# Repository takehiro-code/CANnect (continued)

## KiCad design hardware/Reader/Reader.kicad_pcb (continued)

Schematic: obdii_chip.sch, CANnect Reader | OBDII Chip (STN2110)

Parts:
CP_STN_1: 10uF; CP_Elec_4x5.8; Part Name EEEFP1E100AR; digikeypn PCE4539CT-ND
C_STN_1, C_STN_4, C_STN_5, C_STN_6: 1uF; 0603; Part Name C0603C105K4RACTU; digikeypn 399-7847-1-ND
C_STN_2, C_STN_3: 30pF; CAPC1608X90N; Part Name C0603C300J5GACTU; digikeypn 399-9057-1-ND
J_STN_1, J_STN_2, J_STN_4, J_STN_5, J_STN_6: Header_Pin_2; PinHeader_1x02_P2.54mm_Vertical
LED_STN_1: Status; LED_0603_1608Metric; Part Name 150060RS75000; digikeypn 732-4978-1-ND
LED_STN_2: OBD Activity; LED_0603_1608Metric; Part Name 150060YS75000; digikeypn 732-4981-1-ND
LED_STN_3: Host Activity; LED_0603_1608Metric; Part Name 150060VS75000; digikeypn 732-4980-1-ND
R_STN_1, R_STN_2, R_STN_3: 330; RESC3216X70N; Part Name ERJ-8ENF3300V; digikeypn P330FCT-ND
R_STN_4: 1k; RC1608F102CS; Part Name RC1608F102CS; digikeypn 1276-3484-1-ND
R_STN_5, R_STN_6, R_STN_9, R_STN_13: 100k; RESC1608X55N; Part Name RT0603DRE07100KL; digikeypn 311-2395-1-ND
R_STN_7, R_STN_8: 1.5k; RESC1607X60N; Part Name RC0603FR-071K5L; digikeypn 311-1.50KHRCT-ND
R_STN_10: 500; RESC1508X55N; Part Name MCT0603PD4990DP500; digikeypn 749-1523-1-ND
R_STN_11: 10k; RESC1608X55N; Part Name RT0603FRE0710KL; digikeypn YAG2321CT-ND
R_STN_12: 10; RESC1608X55N; Part Name RE0603FRE0710RL; digikeypn 13-RE0603FRE0710RLCT-ND
SW_STN_1: PTS647SK38SMTR2LFS; Part Name PTS 647 SK38 SMTR2 LFS; digikeypn PTS647SK38SMTR2LFSCT-ND
U_STN_1: STN2120; CANtech-STN2120-QFN-44-1EP_8x8mm; Part Name STN2120
Y_STN_1: ECS-2033-160-AU (16MHz); OSC_ECS-2033-160-AU; Part Name ECS-2033-160-AU (16MHz); digikeypn XC1858CT-ND

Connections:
+3V3: C_STN_1.1, C_STN_5.1, C_STN_6.1, J_STN_4.2, J_STN_5.1, LED_STN_1.2 (A), LED_STN_2.2 (A), LED_STN_3.2 (A), R_STN_4.1, R_STN_5.2, R_STN_6.2, R_STN_7.1, R_STN_8.1, R_STN_9.2, R_STN_11.1, R_STN_12.1, R_STN_13.1, U_STN_1.28 (VDD), U_STN_1.40 (VDD), Y_STN_1.4 (VDD); also elsewhere on the board
/Host/HST_RX: J_STN_1.1, U_STN_1.5 (UART_RX); also elsewhere on the board
/Host/HST_TX: J_STN_1.2, R_STN_4.2, U_STN_1.4 (UART_TX); also elsewhere on the board
/Host/~PWR_CTRL~: U_STN_1.32 (~PWR_CTRL~/GP19); also elsewhere on the board
/Host/~RESET_OBD_HW~: C_STN_4.1, R_STN_2.2, SW_STN_1.2, U_STN_1.12 (~LED_OBD_ACT~/~RST_NVM~/GP22); also elsewhere on the board
/Host/~RESET_OBD_SW~: J_STN_6.1, R_STN_11.2, U_STN_1.18 (~RESET~); also elsewhere on the board
/Host/~SLEEP_OBD~: R_STN_13.2, U_STN_1.27 (~SLEEP~/GP18); also elsewhere on the board
/OBDII Interpreter/Analog_Voltage: U_STN_1.19 (ANALOG_IN); also elsewhere on the board
/OBDII Interpreter/Comparator Transceiver/PWM_RX: U_STN_1.23 (PWM_RX/GP0); also elsewhere on the board
/OBDII Interpreter/Comparator Transceiver/VPW_RX: U_STN_1.22 (VPW_RX/GP1); also elsewhere on the board
/OBDII Interpreter/Comparator Transceiver/~ISO_RX~: U_STN_1.21 (~ISO_RX~/GP5); also elsewhere on the board
/OBDII Interpreter/High Speed CAN Transceiver/HS_CAN_RX: J_STN_2.2, U_STN_1.10 (HS_CAN_RX/GP8); also elsewhere on the board
/OBDII Interpreter/High Speed CAN Transceiver/HS_CAN_TX: J_STN_2.1, U_STN_1.8 (HS_CAN_TX/GP9); also elsewhere on the board
/OBDII Interpreter/ISO 9141/ISO 14230 Transceiver/~ISO_K_TX~: U_STN_1.43 (~ISO_K_TX~/GP6); also elsewhere on the board
/OBDII Interpreter/ISO 9141/ISO 14230 Transceiver/~ISO_L_TX~: U_STN_1.44 (~ISO_L_TX~/GP7); also elsewhere on the board
/OBDII Interpreter/OBDII Chip/J1850_BUS+_TX: U_STN_1.24 (J1850_BUS+_TX/GP2); also elsewhere on the board
/OBDII Interpreter/OBDII Chip/J1850_BUS-_TX: U_STN_1.33 (J1850_BUS-_TX/GP3); also elsewhere on the board
/OBDII Interpreter/OBDII Chip/~J1850_BUS+_VH~: U_STN_1.25 (~J1850_BUS+_VH~/GP4); also elsewhere on the board
unnamed: CP_STN_1.1, U_STN_1.7 (VCAP)
unnamed: C_STN_2.2, U_STN_1.31 (OSC2), Y_STN_1.1 (TRI_STATE)
unnamed: C_STN_3.1, U_STN_1.30 (OSC1), Y_STN_1.3 (OUT)
unnamed: LED_STN_1.1 (K), R_STN_1.1
unnamed: LED_STN_2.1 (K), R_STN_2.1
unnamed: LED_STN_3.1 (K), R_STN_3.1
unnamed: R_STN_1.2, U_STN_1.14 (LED_STATUS/GP26)
unnamed: R_STN_3.2, U_STN_1.13 (~LED_HOST_ACT~/GP24)
unnamed: R_STN_5.1, U_STN_1.9 (MS_CAN_TX/GP11)
unnamed: R_STN_6.1, U_STN_1.11 (MS_CAN_RX/GP10)
unnamed: R_STN_7.2, U_STN_1.42 (SW_CAN_RX/GP12)
unnamed: R_STN_8.2, U_STN_1.41 (SW_CAN_TX/GP13)
unnamed: R_STN_9.1, SW_STN_1.1
unnamed: R_STN_10.1, SW_STN_1.3
Pin4_GnD_Chassis: CP_STN_1.2, C_STN_1.2, C_STN_2.1, C_STN_3.2, C_STN_4.2, C_STN_5.2, C_STN_6.2, J_STN_4.1, J_STN_5.2, J_STN_6.2, R_STN_10.2, U_STN_1.1 (GP28), U_STN_1.2 (GP29), U_STN_1.3 (GP30), U_STN_1.6 (VSS), U_STN_1.15 (GP31), U_STN_1.16 (AV_SS), U_STN_1.20 (GP32), U_STN_1.26 (GP33), U_STN_1.29 (VSS), U_STN_1.37 (GP34), U_STN_1.38 (GP35), U_STN_1.39 (VSS), U_STN_1.45 (PAD), Y_STN_1.2 (GND); also elsewhere on the board
VDDA: R_STN_12.2, U_STN_1.17 (AV_DD)

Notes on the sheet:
LED Indicators
Host Device
16Mhz Oscillator
Reset button

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
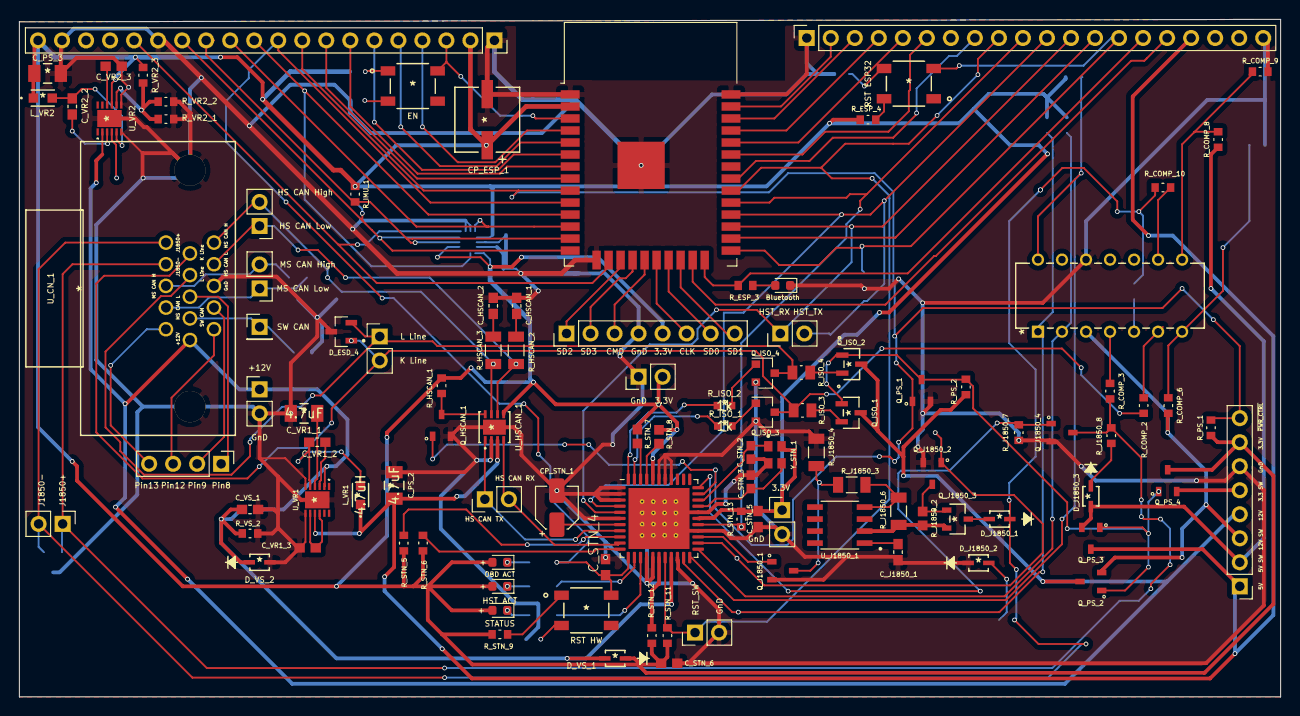
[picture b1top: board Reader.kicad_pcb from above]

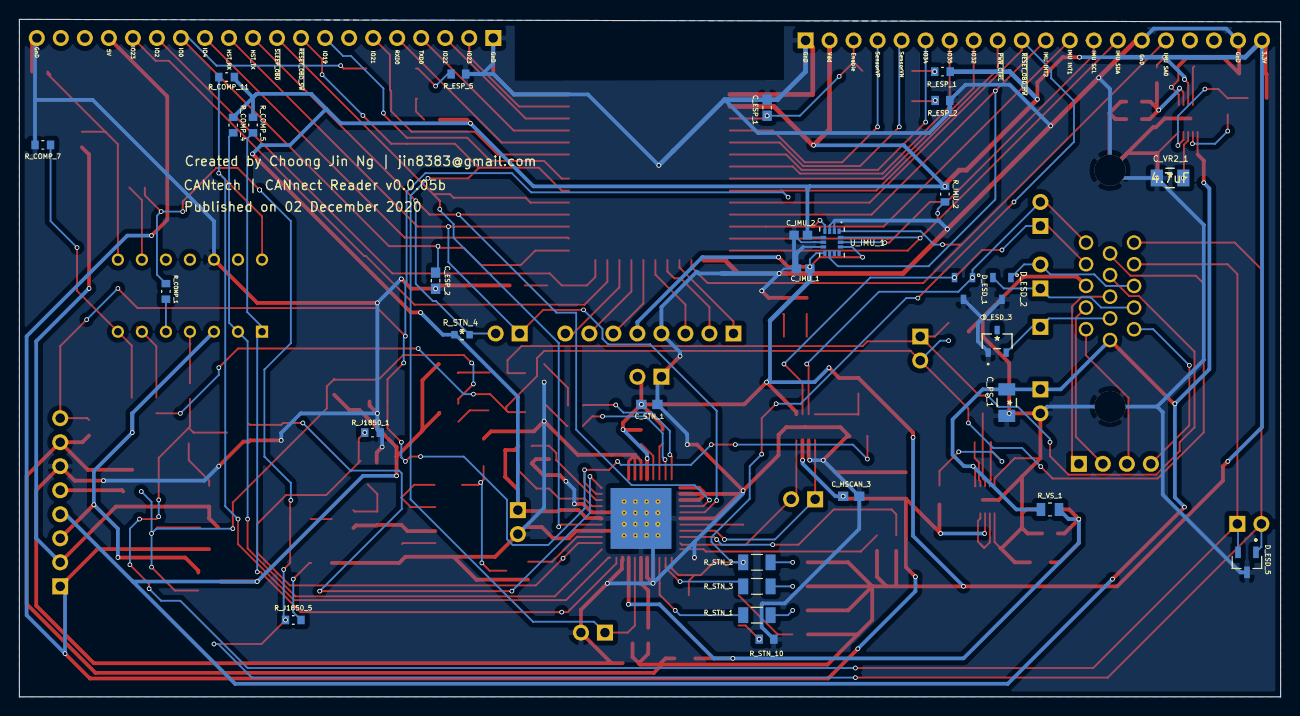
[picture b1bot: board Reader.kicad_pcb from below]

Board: 2 copper layers, 133.4 x 71.6 mm, 137 parts (30 on the bottom side), 115 nets.

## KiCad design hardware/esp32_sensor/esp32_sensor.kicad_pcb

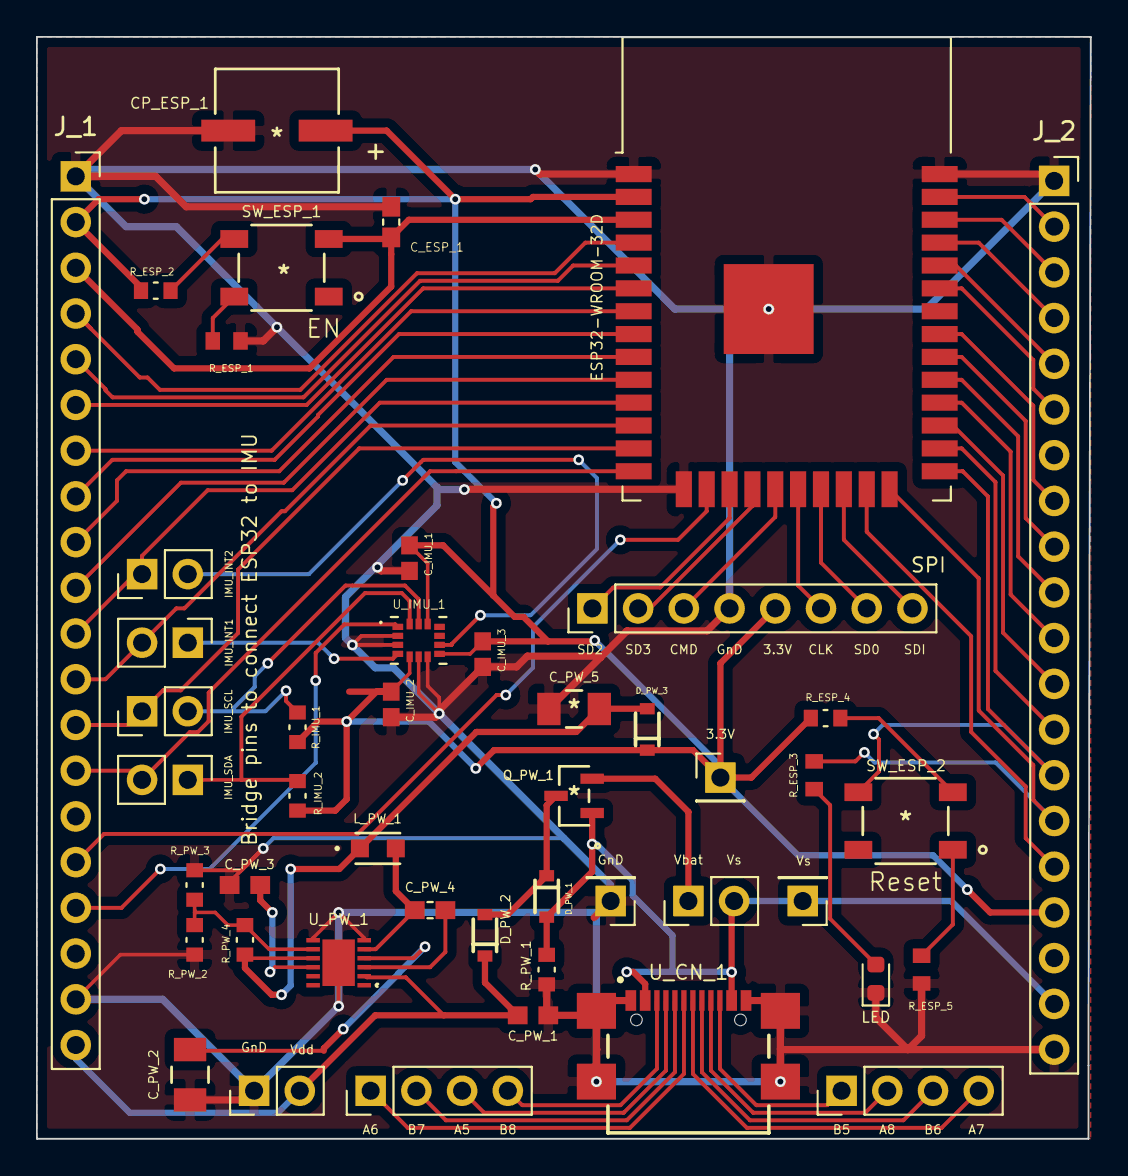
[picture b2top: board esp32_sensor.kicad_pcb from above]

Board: 2 copper layers, 58.5 x 61.2 mm, 47 parts (0 on the bottom side), 63 nets.

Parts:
CP_ESP_1: 100uF; UCB0J101MCL1GS
C_ESP_1: 0.1uF; CAPC1608X90
C_IMU_1, C_IMU_2, C_IMU_3: 100nF; CAPC1608X90N
C_PW_1, C_PW_3: 1uF; 0603
C_PW_2, C_PW_5: 4.7uF; C1206C475K3RACAUTO
C_PW_4: 0.1uF; CAPC1608X90
D_PW_1, D_PW_2, D_PW_3: BAT20JFILM
J_1, J_2: 4157; PinSocket_1x20_P2.54mm_Vertical
J_3: SPI; PinHeader_1x08_P2.54mm_Vertical
J_4: IMU_INT2; PinHeader_1x02_P2.54mm_Vertical
J_5: IMU_INT1; PinHeader_1x02_P2.54mm_Vertical
J_6: IMU_SCL; PinHeader_1x02_P2.54mm_Vertical
J_7: IMU_SDA; PinHeader_1x02_P2.54mm_Vertical
J_CN_1, J_CN_2: Header_Pin_4; PinHeader_1x04_P2.54mm_Vertical
J_CN_3, J_CN_4: Header_Pin_1; PinHeader_1x01_P2.54mm_Vertical
J_PW_1, J_PW_2: Header_Pin_2; PinHeader_1x02_P2.54mm_Vertical
J_PW_3: Header_Pin_1; PinHeader_1x01_P2.54mm_Vertical
LED_ESP_1: LED; LED_0603_1608Metric
L_PW_1: 4.7uH; CV201210-4R7K
Q_PW_1: IRLML5103TRPBF
R_ESP_1, R_ESP_3, R_ESP_5: 500; RESC1508X55N
R_ESP_2, R_ESP_4: 10k; RESC1608X55N
R_IMU_1, R_IMU_2: 4.7k; RESC1608X55N
R_PW_1: 10k; RESC1608X55N
R_PW_2, R_PW_3: 100k; RESC1608X55N
R_PW_4: 115k; RESC1608X55N
SW_ESP_1, SW_ESP_2: PTS647SK38SMTR2LFS
U_CN_1: USB4110-GF-A
U_ESP_1: ESP32-WROOM-32D; ESP32-WROOM-32
U_IMU_1: LSM6DSMTR
U_PW_1: MAX25276ATCA_VY+; MAX25276ATCAVY

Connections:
+3V3: CP_ESP_1.1, C_IMU_1.1, C_IMU_2.1, C_IMU_3.1, D_PW_3.C, J_1.2, J_2.17, J_3.5, J_PW_3.1, R_ESP_2.1, R_ESP_4.2, R_IMU_1.2, R_IMU_2.1, U_ESP_1.2, U_IMU_1.5, U_IMU_1.8, U_IMU_1.12
+BATT: J_PW_1.1, Q_PW_1.2
/ESP32 Chip/ESP32_EN: C_ESP_1.1, J_1.3, SW_ESP_1.3, U_ESP_1.3
/ESP32 Chip/ESP32_Pin4: J_1.4, U_ESP_1.4
/ESP32 Chip/ESP32_Pin5: J_1.5, U_ESP_1.5
/ESP32 Chip/ESP32_Pin6: J_1.6, U_ESP_1.6
/ESP32 Chip/ESP32_Pin7: J_1.7, U_ESP_1.7
/ESP32 Chip/ESP32_Pin8: J_1.8, U_ESP_1.8
/ESP32 Chip/ESP32_Pin9: J_1.9, U_ESP_1.9
/ESP32 Chip/ESP32_Pin10: J_1.10, U_ESP_1.10
/ESP32 Chip/ESP32_Pin11: J_1.11, J_4.1, U_ESP_1.11
/ESP32 Chip/ESP32_Pin12: J_1.12, J_5.2, U_ESP_1.12
/ESP32 Chip/ESP32_Pin13: J_1.13, J_6.1, U_ESP_1.13
/ESP32 Chip/ESP32_Pin14: J_1.14, J_7.2, U_ESP_1.14
/ESP32 Chip/ESP32_Pin16: J_1.16, U_ESP_1.16
/ESP32 Chip/ESP32_Pin17: J_3.1, U_ESP_1.17
/ESP32 Chip/ESP32_Pin18: J_3.2, U_ESP_1.18
/ESP32 Chip/ESP32_Pin19: J_3.3, U_ESP_1.19
/ESP32 Chip/ESP32_Pin20: J_3.6, U_ESP_1.20
/ESP32 Chip/ESP32_Pin21: J_3.7, U_ESP_1.21
/ESP32 Chip/ESP32_Pin22: J_3.8, U_ESP_1.22
/ESP32 Chip/ESP32_Pin23: J_2.16, U_ESP_1.23
/ESP32 Chip/ESP32_Pin24: J_2.15, R_ESP_3.1, U_ESP_1.24
/ESP32 Chip/ESP32_Pin25: J_2.14, SW_ESP_2.4, U_ESP_1.25
/ESP32 Chip/ESP32_Pin26: J_2.13, U_ESP_1.26
/ESP32 Chip/ESP32_Pin27: J_2.12, U_ESP_1.27
/ESP32 Chip/ESP32_Pin28: J_2.11, U_ESP_1.28
/ESP32 Chip/ESP32_Pin29: J_2.10, U_ESP_1.29
/ESP32 Chip/ESP32_Pin30: J_2.9, U_ESP_1.30
/ESP32 Chip/ESP32_Pin31: J_2.8, U_ESP_1.31
/ESP32 Chip/ESP32_Pin33: J_2.6, U_ESP_1.33
/ESP32 Chip/ESP32_Pin36: J_2.3, U_ESP_1.36
/ESP32 Chip/ESP32_Pin37: J_2.2, U_ESP_1.37
/ESP32 Chip/ESP32_RX0: J_2.5, U_ESP_1.34
/ESP32 Chip/ESP32_TX0: J_2.4, U_ESP_1.35
/IMU/IMU_INT1: J_5.1, U_IMU_1.4
/IMU/IMU_INT2: J_4.2, U_IMU_1.9
/IMU/IMU_SCL: J_6.2, R_IMU_1.1, U_IMU_1.13
/IMU/IMU_SDA: J_7.1, R_IMU_2.2, U_IMU_1.14
/IMU/IMU_SDO_SAO: J_1.17, U_IMU_1.1
GND: CP_ESP_1.2, C_ESP_1.2, C_IMU_1.2, C_IMU_2.2, C_IMU_3.2, C_PW_1.1, C_PW_2.2, C_PW_3.1, C_PW_5.2, J_1.1, J_1.19, J_2.1, J_2.20, J_3.4, J_CN_4.1, J_PW_2.1, LED_ESP_1.1, R_ESP_1.2, R_ESP_5.2, R_PW_1.2, R_PW_2.1, R_PW_3.1, U_CN_1.A1/B12, U_CN_1.B1/A12, U_CN_1.S1, U_CN_1.S2, U_CN_1.S3, U_CN_1.S4, U_ESP_1.1, U_ESP_1.15, U_ESP_1.38, U_ESP_1.39, U_IMU_1.2, U_IMU_1.3, U_IMU_1.6, U_IMU_1.7, U_PW_1.6, U_PW_1.7, U_PW_1.13
unnamed: C_PW_2.1, U_PW_1.4
unnamed: C_PW_3.2, U_PW_1.10
unnamed: C_PW_4.1, L_PW_1.2, U_PW_1.5
unnamed: C_PW_4.2, U_PW_1.3
unnamed: C_PW_5.1, D_PW_3.A, L_PW_1.1, R_PW_4.1, U_PW_1.9
unnamed: D_PW_1.C, D_PW_2.A, Q_PW_1.3
unnamed: J_CN_1.1, U_CN_1.B5
unnamed: J_CN_1.2, U_CN_1.A8
unnamed: J_CN_1.3, U_CN_1.B6
unnamed: J_CN_1.4, U_CN_1.A7
unnamed: J_CN_2.1, U_CN_1.A6
unnamed: J_CN_2.2, U_CN_1.B7
unnamed: J_CN_2.3, U_CN_1.A5
unnamed: J_CN_2.4, U_CN_1.B8
unnamed: LED_ESP_1.2, R_ESP_3.2
unnamed: R_ESP_1.1, SW_ESP_1.2
unnamed: R_ESP_2.2, SW_ESP_1.4
unnamed: R_ESP_4.1, SW_ESP_2.3
unnamed: R_ESP_5.1, SW_ESP_2.1
unnamed: R_PW_2.2, R_PW_3.2, R_PW_4.2, U_PW_1.8
VDD: C_PW_1.2, D_PW_2.C, J_1.20, J_PW_2.2, U_PW_1.2
VS: D_PW_1.A, J_2.19, J_CN_3.1, J_PW_1.2, Q_PW_1.1, R_PW_1.1, U_CN_1.A4/B9, U_CN_1.B4/A9

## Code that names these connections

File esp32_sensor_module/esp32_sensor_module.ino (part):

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/**
   ESP32 Pins
*/
#define IMU_INT2      26 // Pin 11
#define IMU_INT1      27 // Pin 12  
#define IMU_SCL       14 // Pin 13
#define IMU_SDA       12 // Pin 14
//#define IMU_SD0       // Not implemented

/**
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
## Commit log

2020-06-15 Add LICENSE
2020-07-18 Progress Review Meeting II PowerPoint Presentation
2020-07-18 Revised Minutes for Progress Review Meeting I
2020-07-20 added comment to test push command
2020-07-21 Test commit and push without building and compiling and without a device.
2020-07-21 Commit1
2020-07-21 Revert "Commit1"
    This reverts commit 7065bfc7
2020-07-21 test commit
2020-07-21 commit test 2
2020-07-21 commit .gitignore
2020-07-22 deleted unnecessary files
2020-07-22 .idea/.name file is automatically created every time. Test commit with build and after running the app.
2020-07-23 implemented issue 34 circle gauge(display only)
2020-08-10 Initial commit on the bluetooth feature.
2020-08-12 Fixed all the bugs on the bluetooth feature.
2020-08-12 Main page, connection status fixed using broadcast receiver.
2020-08-12 Moved android app code into its own directory
2020-08-12 Added Arduino code
2020-08-15 - Back button with title bar fixed and re-implemented. - Main connection status bug fixed.
2020-08-16 Consolidated changes made to alpha-phase and beta-phase software. Added simulator code
2020-08-16 Fixed several bugs. Cleaned up code. Prepared Arduino software for presentation purposes
2020-08-18 Initial Code for Data Parsing of OBD2
2020-08-18 Fixed Hexadecimal conversion operations, changed name field (result[0]) and made DataParsing functions static
2020-08-18 Fixed Incorrect Float Conversion for relevant OBD2 PIDs with division calculation and Engine RPM calculation
2020-08-18 Fixed MAF Sensor Calculation
2020-08-18 Added UI elements and links for OBD2 Data Conversion to Connect Activity
2020-08-18 Modified OBD2 Conversion function to account for CAN ID parameter.
2020-08-19 Initial code for input of buffer data and adaptation to convert from OBD2 to user-friendly format.
2020-08-19 - Dashboard with bluetooth in progress.
2020-08-19 Comment out test sample code in Connect
2020-08-19 Initialize bufferOutput and Fixed user-friendly output on-screen in Connect page.
2020-08-19 Revert "Initialize bufferOutput and Fixed user-friendly output on-screen in Connect page."
    This reverts commit bc168313df1ccfb6f76417c4e00eadd428824f75
2020-08-19 Modified the code where the whole segment of string works.
2020-08-19 Change CAN Bus to attempt initialisation before giving up
2020-08-19 Fixed bugs related to Serial communication
2020-08-19 Add MESSAGE_END for app
2020-08-19 Updated the reader code.
2020-08-25 Bluetooth service implemented. Reading the data in the background completed.
2020-08-26 String rendering in the dashboard utilizing bluetooth service completed.
2020-08-26 Starting service in main activity and bind to it in the dashboard, currently failing.
2020-08-27 Google map implemented in the map activity.
2020-08-27 Fixed map activity title bar.
2020-08-29 Merged all the latest changes including , bluetooth connection, dashboard(data parsing and UI), and map
2020-08-30 Fixed ColorPrimary Spelling, removed old play-services dependencies for version 11, and updated AndroidManifest.xml. Also, fixed back button.
2020-08-30 Fixed the the branch.
2020-08-30 Removed old play-services dependencies for version 11, updated AndroidManifest.xml, style.xml, and fixed back button with the title bar and finally fixed connect layout.
2020-08-31 Adjusted the buffer size with the reader's code.
2020-09-04 implemented graph and gauges
    Should be working. User can view these display by sending data via bluetooth from esp32. Haven't tested it with the actual reader.
2020-09-04 Two threading issue and register/unregister receiver issue are fixed.
2020-09-04 Dashboard line chart in real time implemented for multiple line.
2020-09-10 changed gauge xml and java files
2020-09-11 Commit for test.
2020-09-11 Added a Bluetooth ESP32 simulator
2020-09-12 Fixed character removal of messages at the end.
2020-09-12 Initial commit of AppSeptember, adding settings.
2020-09-13 Combined codes of line chart and gauge, fixed unregisterReceiver.
2020-09-21 Bluetooth sending messages feature implemented.
2020-09-22 Main connection status related to device completed. Socket closing after turning off the bluetooth fixed.
2020-09-22 implemented context menu gauges
    This implementation allowed user to switch between different gagues display. More gauges to be added on later
2020-09-22 modified strings in fragments to match with strings from DataParsing
2020-10-02 Added ESP_NOW feature to reader. Added code for sensor module
2020-10-05 Latest changes for Friday Oct 9 presentation. Chart is still in progress
2020-10-05 Changed chart page which allow a user to see on PID at a time.
2020-10-12 BT Receiving improved and speed enhanced.
2020-10-12 Added 2 new PID(fragments) for gauge display.
2020-10-12 Updated .gitignore for hardware files
2020-10-12 Started work on designing reader schematic with STN 2120
2020-10-16 Current state of sensor components, LSM6DSLTR, ESP32-WROOM-32
2020-10-16 ESP32 development kit module
2020-10-16 Revert "ESP32 development kit module"
    This reverts commit 68f97f29ff1dfc339c1f687ed263d2bd472e4372
2020-10-19 Revised initial schematics for hierarhical structure. Added ESP32, 'Power Supply', Reader MEMs and Power Switch. OBD-II Interpreter is work-in-progress
2020-10-20 Completed schematics for reader
2020-10-22 Updated settings, firebase in map activity, and fixing the crash case of sending messages (3 characters case and float conversion in chart).
2020-10-22 Removed cache library from reader hardware files
2020-10-22 Completed Reader schematics for version 0.0.01
2020-10-22 Minor changes to schematic design for clarity. Added important IC datasheets. Exported schematics and rough gerber files
2020-10-26 Added ESD Protection. Fixed minor bugs on schematic. Attempted placement of components
2020-10-26 Removed BOM rule. Added BOM-related files. Updated libraries. Removed unneeded files
2020-10-26 Fixed bugs on the reader schematic. Exported Schematic Electrical report
2020-10-27 Changed resistor divider for VR2 for cheaper resistors
2020-10-27 Fixed wiring issue on ESD Protection
2020-10-27 Fixed minor bugs in schematic. Completed PCB layout v0.0.1 and exported Gerber files
2020-10-27 Addressed Design Rules problems
2020-10-28 Fixed bugs in schematic. Updated BOM list. Swapped to using ESP32 holder. Updated PCB layout to v0.0.2. Updated schematic to v0.0.4
2020-10-28 Updated .gitignore to ignore ZIP files and rescue-related files
2020-10-28 Fixed positions of components. Fixed silkscreen titles of components
2020-10-28 Made minor adjustments to PCB layout
2020-10-28 Re-exported gerber files
2020-10-29 Cleaned up a few sections for manufacturing
2020-10-29 Fixed minor Silkscreen details. Updated .gitignore to ignore report files. Exported gerber files. Updated PCB layout to v0.0.3
2020-10-29 Updated version number for front silkscreen
2020-10-30 Upload New File
2020-10-30 Sensor Schematic
2020-10-30 Footprint libraries
2020-10-30 6Dof Sensor footprint
2020-10-30 ESP32_Dev Footprint
2020-10-30 Schematic symbols library
2020-10-30 6dof_sensor
2020-10-30 Buck Converter schematic library
2020-10-30 ESP32-WROOM-32-Dev schematic library
2020-11-01 Fixed a component name for header pin
2020-11-10 export log code added
2020-11-18 Add new directory
2020-11-18 Sender (ESP8266)
2020-11-18 Receiver (ESP32)
2020-11-19 Revising reader
2020-11-20 Implemented Diagnostics page as well as added several new PIDs.
2020-11-23 Fixed numerous bugs in design for Reader Schematic and PCB
2020-11-23 Added ESP32 Schematic and PCB design
2020-11-25 Updated schematic and PCB design to v0.0.2 for 2-layer PCB. Added more silkscreen text
2020-11-25 Updated sensor module to v0.0.3. Fixed USB design flaw. Moved polarised capacitor towards inside of the board. Updated via sizes
2020-11-25 Updated silkscreen. Moved silkscreen of header pins to the bottom of PCB
2020-11-25 Updated PCB to v0.0.3b. Fixed tracks and silkscreen
2020-11-27 Fixed a bug in data processing of sensor data.
2020-11-28 Updated reader schematic to v0.0.5 by adding ESP32, removing unused transceivers, fixed design flaws, increased header pins and fixed footprints. Working on reader PCB design
2020-11-28 Revert "Fixed a bug in data processing of sensor data."
    This reverts commit 4c9e5f86
2020-11-30 Implemented simultaneous PIDs request up to 5(table page), 4(gauge page).
2020-11-30 added two new files: DTCArrayAdapter java and xml.
2020-11-30 Revert "Implemented simultaneous PIDs request up to 5(table page), 4(gauge page)."
    This reverts commit 915d3441
2020-11-30 Updated schematic and gerber to v0.0.05. Added ESP32. Removed MS CAN and SW CAN Transceivers. Added silkscreen text to header pins. Improved readability
2020-12-03 Changed capacitor part number for reader
2020-12-03 Started working on ESP32 Sensor Module
2020-12-03 Friction circle and 6DOF code added
2020-12-03 Converted PCB design into a 2-layer PCB for v0.0.5b. Adjusted schematic to use header pins for connector
2020-12-03 Added keep-out area to ESP32 antenna. Updated silkscreen of Reader
2020-12-03 Update reader.ino Merged OBD protocol and requesting pids from app to OBD code.
2020-12-03 Implemented protocols request to OBD for automatic searching of OBD protocols. Added few more pids.
2020-12-03 Fixed compiling issues related to functions. Added hardware flags. Added IMU data structure as expected in app
2020-12-03 Cleaned up existing reader code for readability. Prepared helper functions for sensor module development for reader
2020-12-03 Added some comments to reader.ino
2020-12-04 Update reader.ino randomized sensor values are sent to app.
2020-12-04 Remove unused code. Fixed ranges from generating sample IMUs
2020-12-04 Implemented better way for reader.ino to search for substrings within string. Cleaned up more unused code
2020-12-04 Fixed LEDs for reader
2020-12-04 Friction circle fixes
2020-12-04 Friction circle fixed y value
2020-12-04 Initial LTE/GPS Code for ESP32
2020-12-04 Fixes for export and friction circle
2020-12-04 Implemented notification to user about protocol found or not.
2020-12-04 Enhanced styling in Connect, MainActivity, Settings menu. Fixed MainActivity status bar only connect/disconnect. Included Toast for connection in Connect.
2020-12-04 Enhanced styling in Dashboard, Dashboard_chart (not perfect yet). Fixed Gauge styling. Fixed Bottom navigation in chart, gauge.
2020-12-04 Implemented ESP-NOW for sensor module and reader
2020-12-04 Make changes so that the PIDs still display values after pressing home button.
2020-12-04 bug fixes
2020-12-05 Uncommented code to send information to Firebase.
2020-12-05 Implemented ESP-NOW functionality between reader and sensor module. Implemented demo flag for sensor module
2020-12-07 pitch&roll simulation added
2020-12-07 Cleaned up codes, and improved text styling on gauge page.
2020-12-08 In Connect, issue of tapping Show Pair Devices button that will cause duplicate items have been fixed.
2020-12-08 Added credtis.txt
2020-12-08 Removed toasts in settings, and styling enhanced in CarBrand page.
2020-12-08 Code cleanup, comments, timeout change to 2500 ms and RST pin function added.
2020-12-08 Make axis dynamic according to the value. Implemented light, dark theme of chart.
2020-12-08 minor changes
2020-12-08 Changed 2 line colors.
2021-06-08 Updated README.md file.
2021-06-08 Fixing README.md
2021-10-25 Updating README.md
